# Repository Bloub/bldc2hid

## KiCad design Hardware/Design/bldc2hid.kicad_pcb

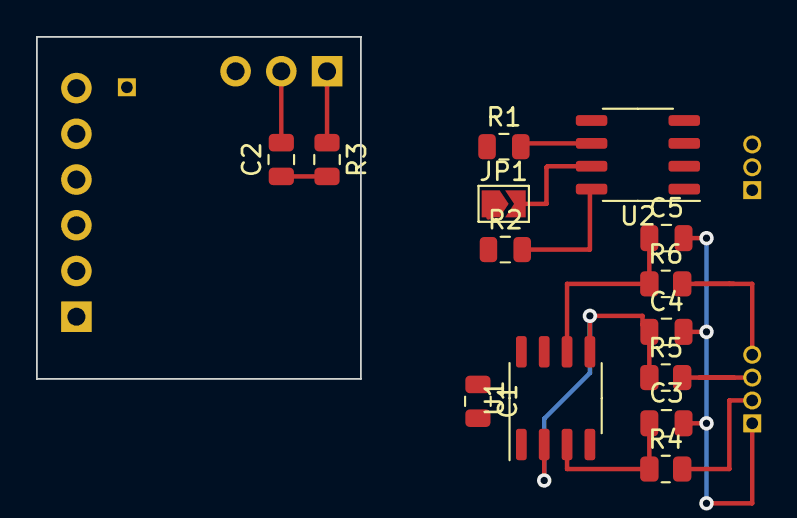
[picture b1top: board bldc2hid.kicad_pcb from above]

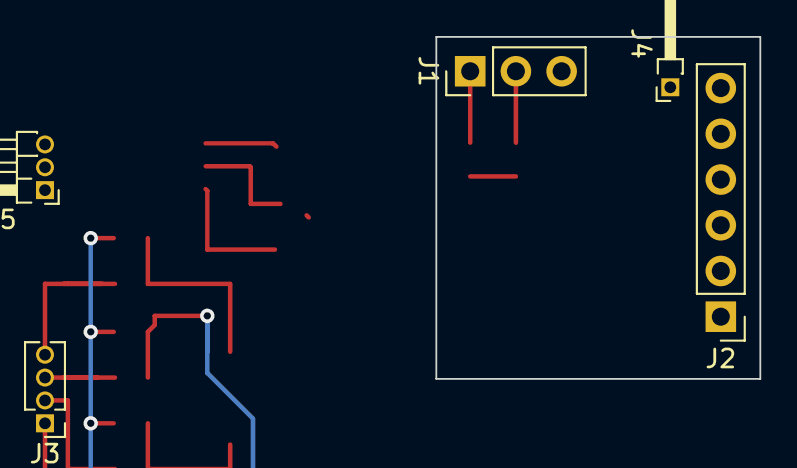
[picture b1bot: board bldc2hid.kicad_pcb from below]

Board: 2 copper layers, 18.0 x 19.0 mm, 19 parts (5 on the bottom side), 18 nets.

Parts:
C1, C2: C; C_0805_2012Metric
C3, C4, C5: 30n; C_0805_2012Metric
J1: Conn_01x03_Female; PinHeader_1x03_P2.54mm_Vertical
J2: Conn_01x06_Female; PinHeader_1x06_P2.54mm_Vertical
J3: Conn_01x04_Female; PinHeader_1x04_P1.27mm_Vertical
J4: Conn_01x01_Female; PinHeader_1x01_P1.27mm_Horizontal
J5: Conn_01x03_Female; PinHeader_1x03_P1.27mm_Horizontal
JP1: SolderJumper_2_Open; SolderJumper-2_P1.3mm_Open_TrianglePad1.0x1.5mm
R1: 33; R_0805_2012Metric
R2: 100; R_0805_2012Metric
R3: 22M; R_0805_2012Metric
R4, R5, R6: 10K; R_0805_2012Metric
U1: LT1492; SO-8_3.9x4.9mm_P1.27mm
U2: WS2811; SO-8_3.9x4.9mm_P1.27mm

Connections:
+5V: C1.1, J1.1, JP1.1, R2.1, R3.1, U1.8
CapSense: C2.1, J2.6, J4.1, R3.2
Direction: J2.2, U1.7
GND: C1.2, C2.2, C3.2, C4.2, C5.2, J1.2, J3.1, U1.4, U2.4
L1: J3.2, R4.2
L2: J3.3, R5.2
L3: J3.4, R6.2
LedCmd: J2.1, R1.1
unnamed: C3.1, R4.1, U1.3
unnamed: C4.1, R5.1, U1.2, U1.5
unnamed: C5.1, R6.1, U1.6
unnamed: J5.1, U2.1
unnamed: J5.2, U2.2
unnamed: J5.3, U2.3
unnamed: JP1.2, U2.7
unnamed: R1.2, U2.6
unnamed: R2.2, U2.8
Threshold: J2.3, U1.1

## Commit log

2021-03-04 First draft of hardware (WIP)
2021-03-04 Folder ordering
2021-03-04 Datasheet added
2021-03-17 Comparaison faite avec les 3 phases
2021-03-17 Modelica simulation added
2021-06-02 LTSpice simulation for bldc -> 2 signals added
2021-06-04 Simulation updated with low-pass filter on output
